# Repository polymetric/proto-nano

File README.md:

# Proto Nano

This is an Arduino Nano clone I made in late May 2018. It was pretty
much solely designed so that I could learn KiCad and SMD soldering, but
I also kind of wanted an Arduino made in KiCad anyway. This one has its
problems, though, so I'll make a new one in the future that addresses
these. Problems include, but are not limited to:

- Poor routing job, leading to far more vias than necessary
- Tantalum capacitors are used, which could be substituted for multiple
smaller ceramic capacitors.
- The QFP chip could be replaced with the QFN equivalent, which is
slightly more compact and easier to handle with tweezers.
- I forgot to add tags on the LEDs. The LEDs are, from top to bottom:
RX, TX, PWR, and D13.

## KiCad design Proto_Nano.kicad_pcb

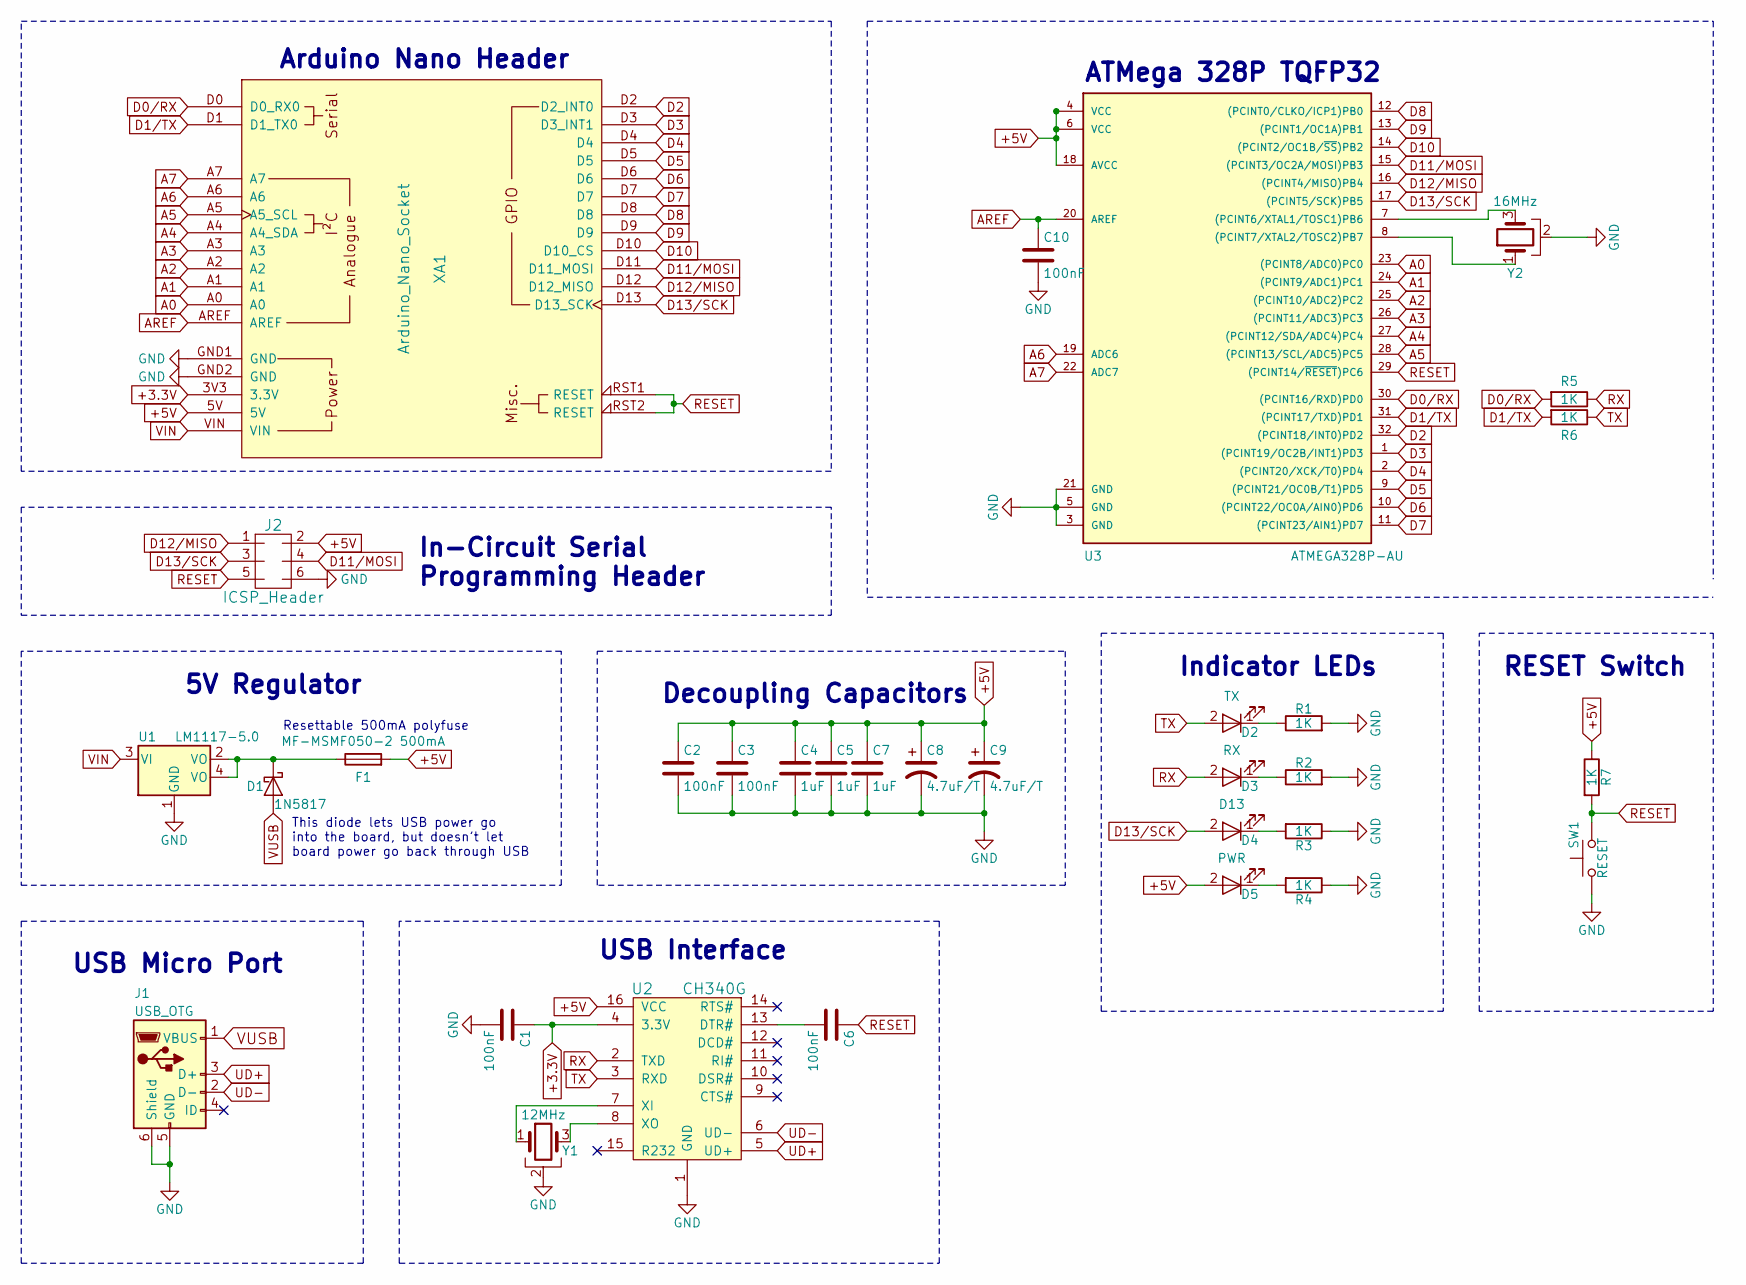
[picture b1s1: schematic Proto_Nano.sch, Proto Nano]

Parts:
C1, C2, C3, C6, C10: 100nF; C_0603
C4, C5, C7: 1uF; C_0603
C8, C9: 4.7uF/T; CP_Tantalum_Case-A_EIA-3216-18_Reflow
D1: 1N5817; D_SOD-123
D2: TX; LED_0603
D3: RX; LED_0603
D4: D13; LED_0603
D5: PWR; LED_0603
F1: MF-MSMF050-2 500mA; 1812_PTC_Fuse
J1: USB_OTG; USB_Micro-B_Molex-105017-0001
J2: ICSP_Header; Pin_Header_Straight_2x03_Pitch2.54mm
R1, R2, R3, R4, R5, R6, R7: 1K; R_0603
SW1: RESET; SW_SPST_FSMSM
U1: LM1117-5.0; SOT-223
U2: CH340G; SOP-16_4.4x10.4mm_Pitch1.27mm
U3: ATMEGA328P-AU; TQFP-32_7x7mm_Pitch0.8mm
XA1: Arduino_Nano_Socket
Y1: 12MHz; murata-resonator_SMD_CSTCE16M0V53-R0
Y2: 16MHz; murata-resonator_SMD_CSTCE16M0V53-R0

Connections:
+3.3V: C1.1, U2.4 (3.3V), XA1.3V3 (3.3V)
+5V: C2.1, C3.1, C4.1, C5.1, C7.1, C8.1, C9.1, D5.2 (A), F1.2, J2.2, R7.1, U2.16 (VCC), U3.4 (VCC), U3.6 (VCC), U3.18 (AVCC), XA1.5V
A0: U3.23 ((PCINT8/ADC0)PC0), XA1.A0
A1: U3.24 ((PCINT9/ADC1)PC1), XA1.A1
A2: U3.25 ((PCINT10/ADC2)PC2), XA1.A2
A3: U3.26 ((PCINT11/ADC3)PC3), XA1.A3
A4: U3.27 ((PCINT12/SDA/ADC4)PC4), XA1.A4 (A4_SDA)
A5: U3.28 ((PCINT13/SCL/ADC5)PC5), XA1.A5 (A5_SCL)
A6: U3.19 (ADC6), XA1.A6
A7: U3.22 (ADC7), XA1.A7
AREF: C10.1, U3.20 (AREF), XA1.AREF
D0/RX: R5.2, U3.30 ((PCINT16/RXD)PD0), XA1.D0 (D0_RX0)
D1/TX: R6.2, U3.31 ((PCINT17/TXD)PD1), XA1.D1 (D1_TX0)
D2: U3.32 ((PCINT18/INT0)PD2), XA1.D2 (D2_INT0)
D3: U3.1 ((PCINT19/OC2B/INT1)PD3), XA1.D3 (D3_INT1)
D4: U3.2 ((PCINT20/XCK/T0)PD4), XA1.D4
D5: U3.9 ((PCINT21/OC0B/T1)PD5), XA1.D5
D6: U3.10 ((PCINT22/OC0A/AIN0)PD6), XA1.D6
D7: U3.11 ((PCINT23/AIN1)PD7), XA1.D7
D8: U3.12 ((PCINT0/CLKO/ICP1)PB0), XA1.D8
D9: U3.13 ((PCINT1/OC1A)PB1), XA1.D9
D10: U3.14 ((PCINT2/OC1B/~SS~)PB2), XA1.D10 (D10_CS)
D11/MOSI: J2.4, U3.15 ((PCINT3/OC2A/MOSI)PB3), XA1.D11 (D11_MOSI)
D12/MISO: J2.1, U3.16 ((PCINT4/MISO)PB4), XA1.D12 (D12_MISO)
D13/SCK: D4.2 (A), J2.3, U3.17 ((PCINT5/SCK)PB5), XA1.D13 (D13_SCK)
GND: C1.2, C2.2, C3.2, C4.2, C5.2, C7.2, C8.2, C9.2, C10.2, J1.5 (GND), J1.6 (Shield), J2.6, R1.2, R2.2, R3.1, R4.1, SW1.1, U1.1 (GND), U2.1 (GND), U3.3 (GND), U3.5 (GND), U3.21 (GND), XA1.GND1 (GND), XA1.GND2 (GND), Y1.2, Y2.2
unnamed: C6.2, U2.13 (DTR#)
unnamed: D1.1 (K), F1.1, U1.2 (VO), U1.4 (VO)
unnamed: D2.1 (K), R1.1
unnamed: D3.1 (K), R2.1
unnamed: D4.1 (K), R3.2
unnamed: D5.1 (K), R4.2
unnamed: U2.7 (XI), Y1.1
unnamed: U2.8 (XO), Y1.3
unnamed: U3.7 ((PCINT6/XTAL1/TOSC1)PB6), Y2.3
unnamed: U3.8 ((PCINT7/XTAL2/TOSC2)PB7), Y2.1
RESET: C6.1, J2.5, R7.2, SW1.2, U3.29 ((PCINT14/~RESET~)PC6), XA1.RST1 (RESET), XA1.RST2 (RESET)
RX: D3.2 (A), R5.1, U2.2 (TXD)
TX: D2.2 (A), R6.1, U2.3 (RXD)
UD+: J1.3 (D+), U2.5 (UD+)
UD-: J1.2 (D-), U2.6 (UD-)
VIN: U1.3 (VI), XA1.VIN
VUSB: D1.2 (A), J1.1 (VBUS)

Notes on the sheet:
USB Interface
USB Micro Port
RESET Switch
ATMega 328P TQFP32
5V Regulator
This diode lets USB power go into the board, but doesn't let board power go back through USB
Resettable 500mA polyfuse
Indicator LEDs
Decoupling Capacitors
In-Circuit Serial Programming Header
Arduino Nano Header

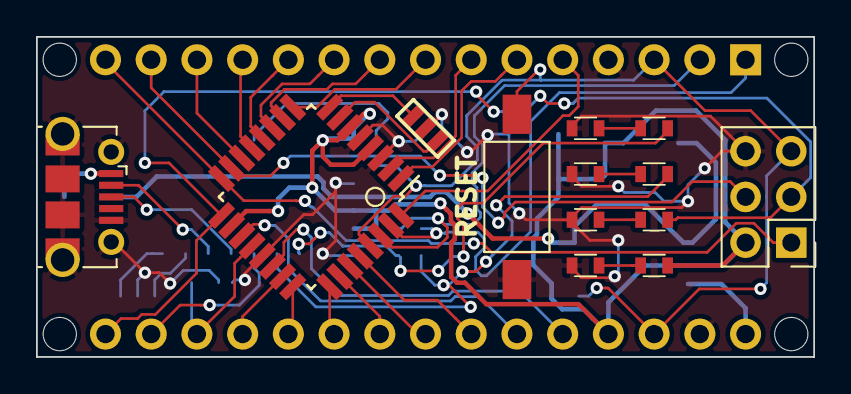
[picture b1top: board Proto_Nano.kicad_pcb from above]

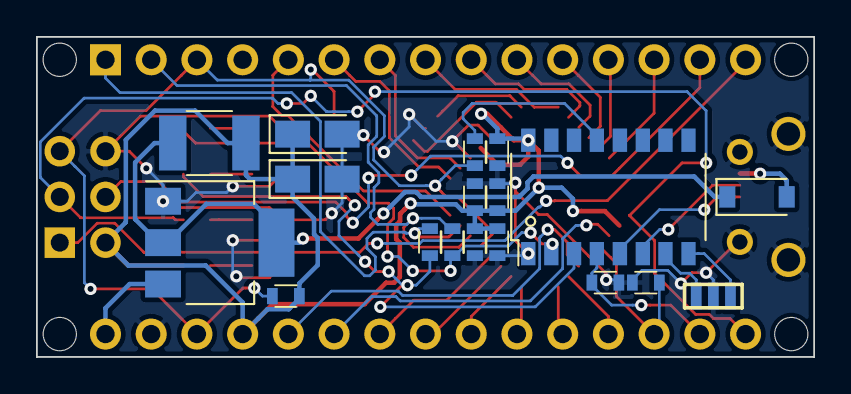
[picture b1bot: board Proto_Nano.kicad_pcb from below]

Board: 2 copper layers, 43.2 x 17.8 mm, 32 parts (18 on the bottom side), 43 nets.

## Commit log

2018-05-30 add gerbers
2018-05-30 move a via so it's not blocking some silkscreen text
2018-06-08 zip gerbers and finish assembly diagram
2018-06-08 github -> bitbucket
2018-06-08 add readme and fix gitignore
2018-06-08 remove ignored files
2018-06-08 add localized libraries
2018-06-08 fix a Thing on the schematic replace the symbol for the ICSP header with a more logical one, and move it to a different place in the schematic

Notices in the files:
Proto_Nano.sch:
License: CC-BY-SA-4.0
creativecommons.org/licenses/by-sa-4.0
